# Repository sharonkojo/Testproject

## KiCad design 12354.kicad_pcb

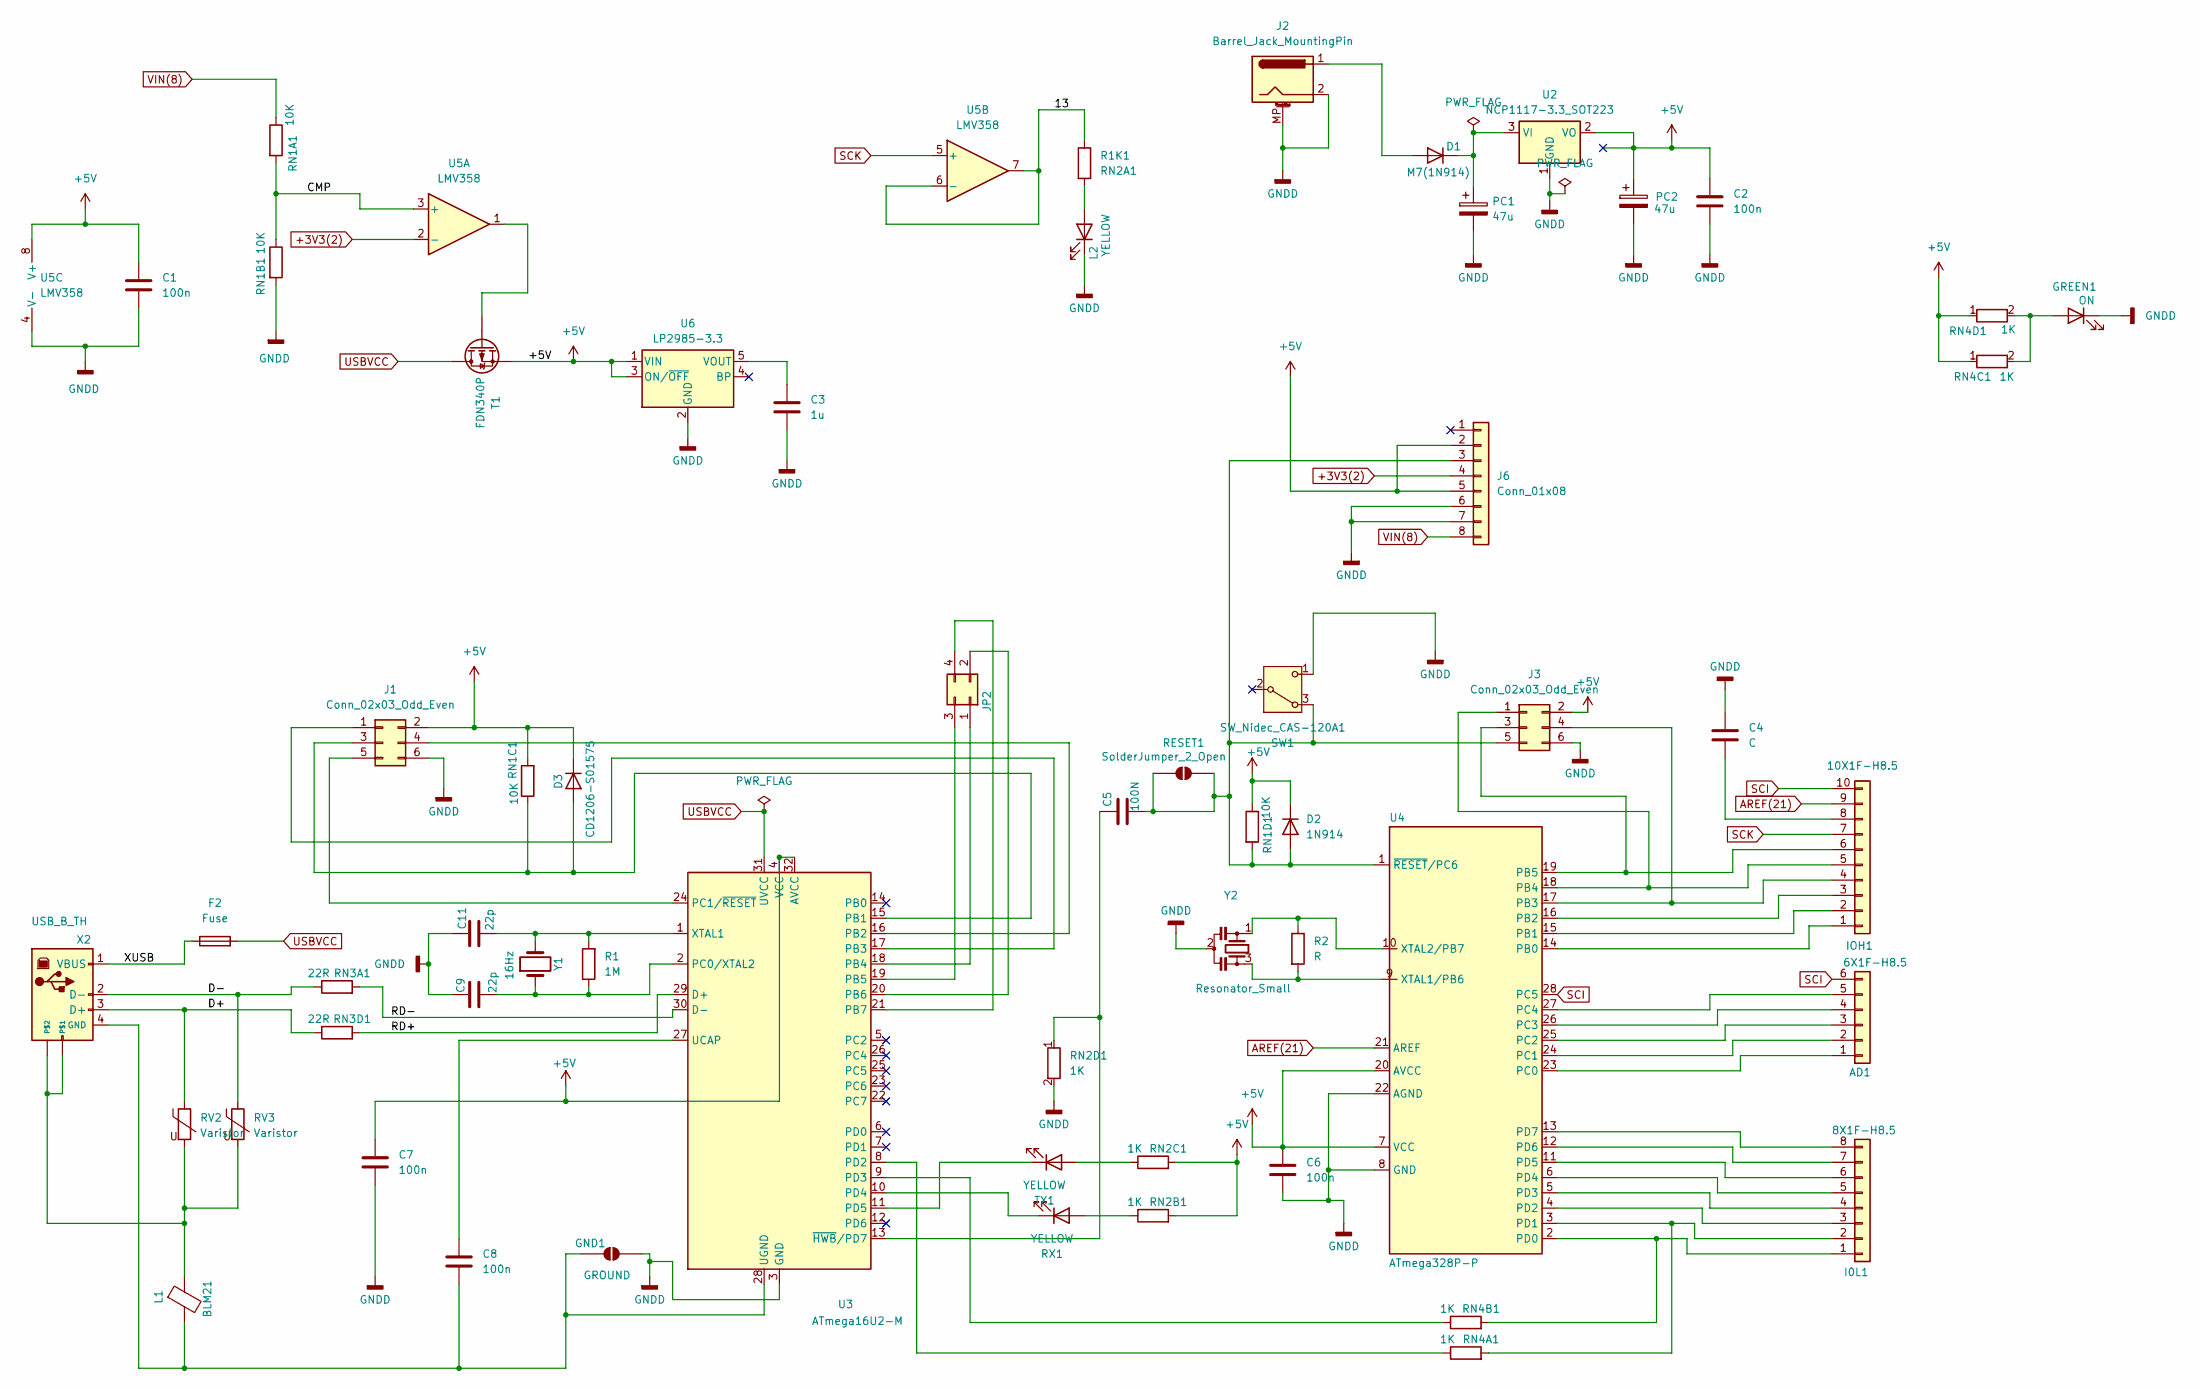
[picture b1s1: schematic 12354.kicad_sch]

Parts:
AD1: 6X1F-H8.5; PinSocket_1x06_P2.54mm_Vertical
C1, C6, C7, C8: 100n; C_0603_1608Metric_Pad1.08x0.95mm_HandSolder
C2: 100n; C_0805_2012Metric_Pad1.18x1.45mm_HandSolder
C3: 1u; C_01005_0402Metric
C4: C; C_0603_1608Metric_Pad1.08x0.95mm_HandSolder
C5: 100N; C_0603_1608Metric_Pad1.08x0.95mm_HandSolder
C9, C11: 22p; C_0603_1608Metric_Pad1.08x0.95mm_HandSolder
D1: M7(1N914); D_SC-80
D2: 1N914; D_SOD-123
D3: CD1206-S01575; D_SOD-123
F2: Fuse; Fuse_2920_7451Metric
GND1: GROUND; SolderJumper-2_P1.3mm_Open_RoundedPad1.0x1.5mm
GREEN1: ON; LED_0805_2012Metric_Pad1.15x1.40mm_HandSolder
I0L1: 8X1F-H8.5; PinHeader_1x08_P2.54mm_Vertical
IOH1: 10X1F-H8.5; PinSocket_1x10_P2.54mm_Vertical
J1: Conn_02x03_Odd_Even; PinHeader_2x03_P2.54mm_Vertical_SMD
J2: Barrel_Jack_MountingPin; BarrelJack_Horizontal
J3: Conn_02x03_Odd_Even; PinHeader_2x03_P2.54mm_Vertical
J6: Conn_01x08; PinSocket_1x08_P2.54mm_Vertical
JP2: Conn_02x02_Odd_Even; PinSocket_2x02_P2.54mm_Vertical
L1: BLM21; L_0805_2012Metric_Pad1.05x1.20mm_HandSolder
L2: YELLOW; LED_0805_2012Metric_Pad1.15x1.40mm_HandSolder
PC1, PC2: 47u; CP_Elec_6.3x5.4
R1: 1M; R_0201_0603Metric_Pad0.64x0.40mm_HandSolder
R1K1: RN2A1; R_0201_0603Metric_Pad0.64x0.40mm_HandSolder
R2: R; R_0201_0603Metric_Pad0.64x0.40mm_HandSolder
RESET1: SolderJumper_2_Open; SolderJumper-2_P1.3mm_Open_RoundedPad1.0x1.5mm
RN1A1, RN1B1, RN1D1: 10K; R_0201_0603Metric_Pad0.64x0.40mm_HandSolder
RN1C1: 10K; R_0805_2012Metric_Pad1.20x1.40mm_HandSolder
RN2B1, RN2C1, RN2D1, RN4A1, RN4B1, RN4C1, RN4D1: 1K; R_0201_0603Metric_Pad0.64x0.40mm_HandSolder
RN3A1, RN3D1: 22R; R_0201_0603Metric_Pad0.64x0.40mm_HandSolder
RV2, RV3: Varistor; R_0201_0603Metric_Pad0.64x0.40mm_HandSolder
RX1: YELLOW; LED_0805_2012Metric_Pad1.15x1.40mm_HandSolder
SW1: SW_Nidec_CAS-120A1; SW_Push_1P1T_NO_CK_PTS125Sx43SMTR
T1: FDN340P; SOT-23
TX1: YELLOW; LED_0805_2012Metric_Pad1.15x1.40mm_HandSolder
U2: NCP1117-3.3_SOT223; SOT-223-3_TabPin2
U3: ATmega16U2-M; QFN-32-1EP_5x5mm_P0.5mm_EP3.3x3.3mm
U4: ATmega328P-P; DIP-28_W7.62mm
U5: LMV358; MSOP-8_3x3mm_P0.65mm
U6: LP2985-3.3; SOT-23-5
X2: USB_B_TH; USB_B_TE_5787834_Vertical
Y1: 16Hz; Crystal_HC49-4H_Vertical
Y2: Resonator_Small; Resonator_SMD_Murata_CSTxExxV-3Pin_3.0x1.1mm_HandSoldering

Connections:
+3V3(2): J6.4, U5.2 (-); also elsewhere on the board
+5V: C1.1, C2.1, C6.1, C7.1, D2.1 (K), D3.1 (K), J1.2, J3.2, J6.2, J6.5, PC2.1, RN1C1.2, RN1D1.1, RN2B1.2, RN2C1.2, RN4C1.1, RN4D1.1, T1.2 (S), U2.2 (VO), U3.4 (VCC), U3.32 (AVCC), U4.7 (VCC), U4.20 (AVCC), U5.8 (V+), U6.1 (VIN), U6.3 (ON/~OFF); also elsewhere on the board
/13: R1K1.1, U5.6 (-), U5.7
/CMP: RN1A1.2, RN1B1.1, U5.3 (+)
/D+: RN3D1.1, RV2.1, X2.3 (D+)
/D-: RN3A1.1, RV3.1, X2.2 (D-)
/RD+: RN3D1.2, U3.29 (D+)
/RD-: RN3A1.2, U3.30 (D-)
/XUSB: F2.1, X2.1 (VBUS)
AREF(21): IOH1.9, U4.21 (AREF)
GNDD: C1.2, C2.2, C3.2, C4.2, C6.2, C7.2, C9.1, C11.1, GND1.2 (B), GREEN1.1 (K), J1.6, J2.2, J2.MP (MountPin), J3.6, J6.6, J6.7, L2.1 (K), PC1.2, PC2.2, RN1B1.2, RN2D1.2, SW1.1 (C_1), U2.1 (GND), U3.3 (GND), U3.33 (GND), U4.8 (GND), U4.22 (AGND), U5.4 (V-), U6.2 (GND), Y2.2; also elsewhere on the board
unnamed: AD1.1, U4.23 (PC0)
unnamed: AD1.2, U4.24 (PC1)
unnamed: AD1.3, U4.25 (PC2)
unnamed: AD1.4, U4.26 (PC3)
unnamed: AD1.5, U4.27 (PC4)
unnamed: D1.2 (A), J2.1
unnamed: D1.1 (K), PC1.1, U2.3 (VI)
unnamed 18: C5.2, D2.2 (A), J3.5, J6.3, RESET1.1 (A), RESET1.2 (B), RN1D1.2, SW1.3 (A), U4.1 (~RESET/PC6); also elsewhere on the board
unnamed: D3.2 (A), J1.3, RN1C1.1, U3.15 (PB1)
unnamed: C8.2, GND1.1 (A), L1.2, U3.28 (UGND), X2.4 (GND)
unnamed: GREEN1.2 (A), RN4C1.2, RN4D1.2
unnamed: I0L1.1, RN4B1.2, U4.2 (PD0)
unnamed: I0L1.2, RN4A1.2, U4.3 (PD1)
unnamed: I0L1.3, U4.4 (PD2)
unnamed: I0L1.4, U4.5 (PD3)
unnamed: I0L1.5, U4.6 (PD4)
unnamed: I0L1.6, U4.11 (PD5)
unnamed: I0L1.7, U4.12 (PD6)
unnamed: I0L1.8, U4.13 (PD7)
unnamed: IOH1.1, U4.14 (PB0)
unnamed: IOH1.2, U4.15 (PB1)
unnamed: IOH1.3, U4.16 (PB2)
unnamed: IOH1.4, J3.4, U4.17 (PB3)
unnamed: IOH1.5, J3.1, U4.18 (PB4)
unnamed: IOH1.6, J3.3, U4.19 (PB5)
unnamed: C4.1, IOH1.8
unnamed: J1.1, U3.17 (PB3)
unnamed: J1.4, U3.16 (PB2)
unnamed: J1.5, U3.24 (PC1/~RESET)
unnamed: JP2.1, U3.18 (PB4)
unnamed: JP2.2, U3.20 (PB6)
unnamed: JP2.3, U3.19 (PB5)
unnamed: JP2.4, U3.21 (PB7)
unnamed: L2.2 (A), R1K1.2
unnamed: RN2B1.1, RX1.2 (A)
unnamed: RX1.1 (K), U3.10 (PD4)
unnamed: T1.1 (G), U5.1
unnamed: RN2C1.1, TX1.2 (A)
unnamed: TX1.1 (K), U3.11 (PD5)
unnamed: C9.2, R1.1, U3.2 (PC0/XTAL2), Y1.1
unnamed: RN4A1.1, U3.8 (PD2)
unnamed: RN4B1.1, U3.9 (PD3)
unnamed: C8.1, U3.27 (UCAP)
unnamed: C11.2, R1.2, U3.1 (XTAL1), Y1.2
unnamed: C5.1, RN2D1.1, U3.13 (~HWB/PD7)
unnamed: R2.2, U4.9 (XTAL1/PB6), Y2.3
unnamed: R2.1, U4.10 (XTAL2/PB7), Y2.1
unnamed: C3.1, U6.5 (VOUT)
unnamed: L1.1, RV2.2, RV3.2, X2.
SCI: AD1.6, IOH1.10, U4.28 (PC5)
SCK: IOH1.7, U5.5 (+)
USBVCC: F2.2, T1.3 (D), U3.31 (UVCC)
VIN(8): J6.8, RN1A1.1; also elsewhere on the board

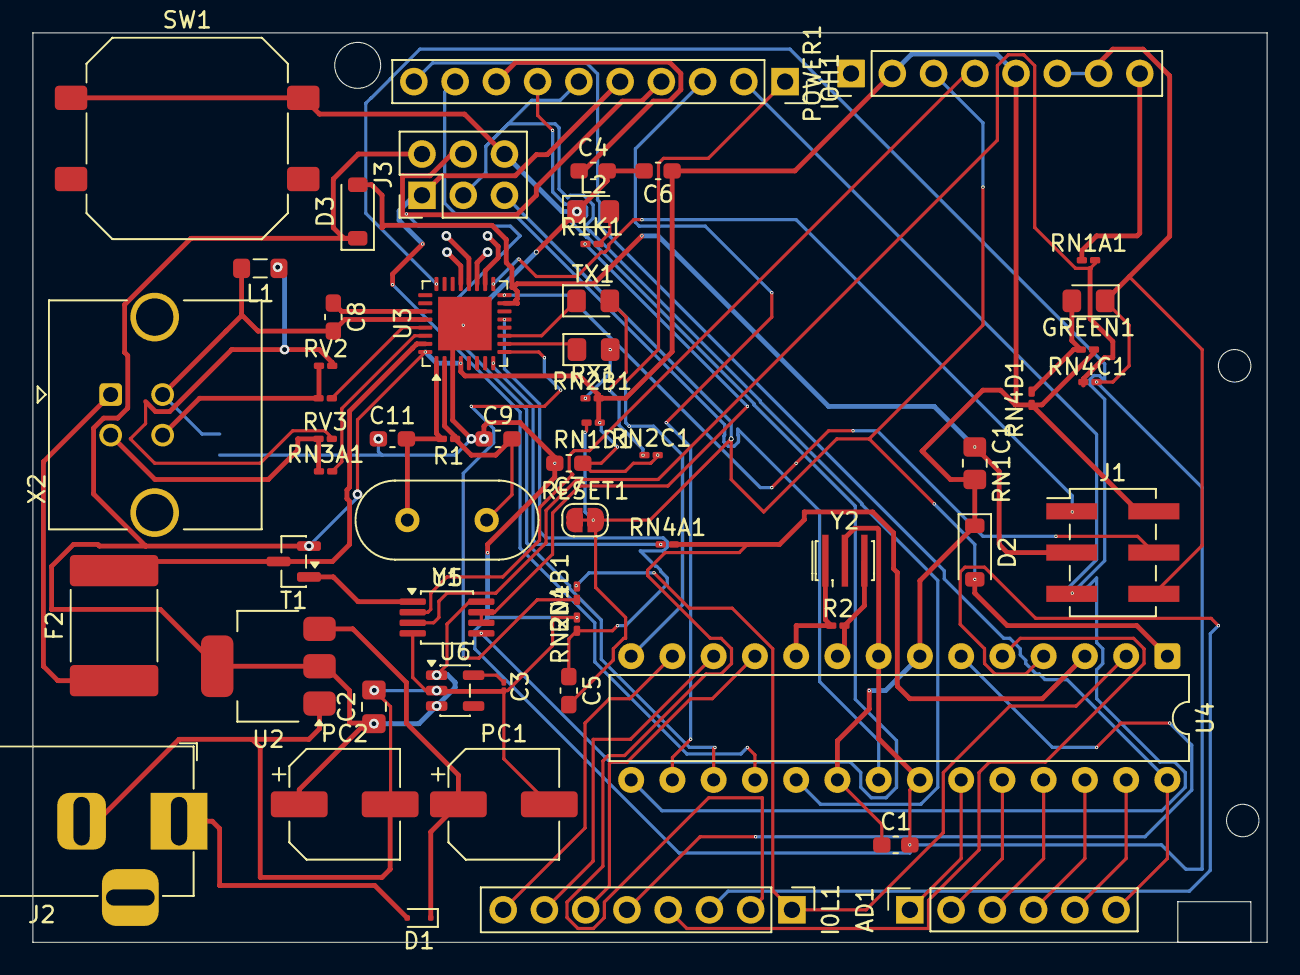
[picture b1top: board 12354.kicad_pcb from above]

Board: 2 copper layers, 76.0 x 56.0 mm, 58 parts (1 on the bottom side), 60 nets.

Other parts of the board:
POWER1: 8X1F-H8.5; PinHeader_1x08_P2.54mm_Vertical

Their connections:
+3V3(2): POWER1.4; also elsewhere on the board
+5V: POWER1.2, POWER1.5; also elsewhere on the board
GNDD: POWER1.6, POWER1.7; also elsewhere on the board
unnamed 18: POWER1.3; also elsewhere on the board
VIN(8): POWER1.8; also elsewhere on the board
